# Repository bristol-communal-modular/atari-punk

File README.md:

# Atari Punk Console

A KiCAD project for the Atari Punk Console

## Contact

Drop me an email at guy@rumblesan.com

## License

This work is licensed under a [Creative Commons Attribution 4.0 International License]("http://creativecommons.org/licenses/by/4.0/")

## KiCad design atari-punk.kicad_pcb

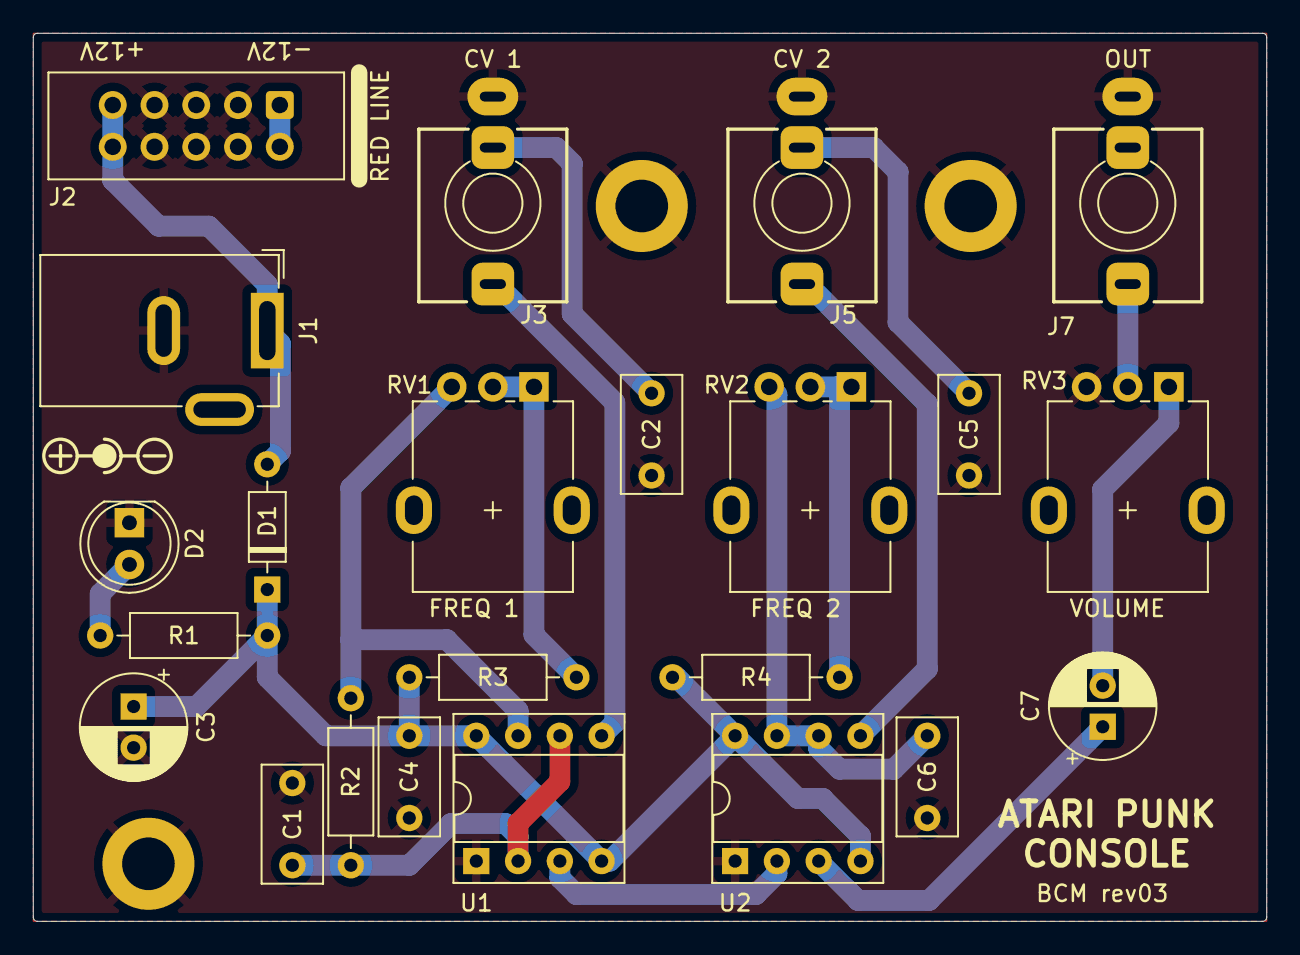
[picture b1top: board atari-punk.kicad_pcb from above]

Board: 2 copper layers, 75.0 x 54.0 mm, 26 parts (0 on the bottom side), 17 nets.

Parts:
C1: 10nF; C_Rect_L7.0mm_W3.5mm_P5.00mm
C2, C4, C5, C6: 100nF; C_Rect_L7.0mm_W3.5mm_P5.00mm
C3: 1uF; CP_Radial_D6.3mm_P2.50mm
C7: 10uF; CP_Radial_D6.3mm_P2.50mm
D1: 1N5818; D_DO-35_SOD27_P7.62mm_Horizontal
D2: LED; LED_D5.0mm
H1, H2, H3: MountingHole_Pad; MountingHole_3.2mm_M3_DIN965_Pad
J1: Barrel_Jack_Switch; BarrelJack_GCT_DCJ200-10-A_Horizontal
J2: Eurorack_Power_Small; Eurorack_PowerHeader_2x05_P2.54mm_Bare
J3: CV1; Jack_3.5mm_QingPu_WQP-PJ398SM_Vertical
J5: CV2; Jack_3.5mm_QingPu_WQP-PJ398SM_Vertical
J7: AUDIO_OUT; Jack_3.5mm_QingPu_WQP-PJ398SM_Vertical
R1: 3k3; R_Axial_DIN0207_L6.3mm_D2.5mm_P10.16mm_Horizontal
R2, R3, R4: 1k; R_Axial_DIN0207_L6.3mm_D2.5mm_P10.16mm_Horizontal
RV1, RV2: 470kA; Potentiometer_Alpha_RD901F-40-00D_Single_Vertical
RV3: 100kA; Potentiometer_Alpha_RD901F-40-00D_Single_Vertical
U1, U2: LM555xN; DIP-8_W7.62mm_Socket

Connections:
GND: C1.2, C2.2, C3.2, C4.2, C5.2, C6.2, D2.1 (K), H1.1, H2.1, H3.1, J1.2, J2.3 (GND), J2.4 (GND), J2.5 (GND), J2.6 (GND), J2.7 (GND), J2.8 (GND), J3.S, J5.S, J7.S, RV3.3, U1.1 (GND), U2.1 (GND)
unnamed: C1.1, R2.1, U1.2 (TR), U1.6 (THR)
unnamed: C2.1, J3.TN
unnamed: C5.1, J5.TN
unnamed: C6.1, RV2.3, U2.6 (THR), U2.7 (DIS)
unnamed: C7.1, U2.3 (Q)
unnamed: C7.2, RV3.1
unnamed: D1.2 (A), J1.1, J2.9 (+12V), J2.10 (+12V)
unnamed: D2.2 (A), R1.2
unnamed: J3.T, U1.5 (CV)
unnamed: J5.T, U2.5 (CV)
unnamed: J7.T, RV3.2
unnamed: R2.2, RV1.3, U1.7 (DIS)
unnamed: R3.2, RV1.1, RV1.2
unnamed: R4.2, RV2.1, RV2.2
unnamed: U1.3 (Q), U2.2 (TR)
VCC: C3.1, C4.1, D1.1 (K), R1.1, R3.1, R4.1, U1.4 (R), U1.8 (VCC), U2.4 (R), U2.8 (VCC)

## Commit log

2022-04-22 Changing diodes
2022-04-22 Adding readme
2022-05-15 Fixing for rev2
2022-11-02 Updating layout
